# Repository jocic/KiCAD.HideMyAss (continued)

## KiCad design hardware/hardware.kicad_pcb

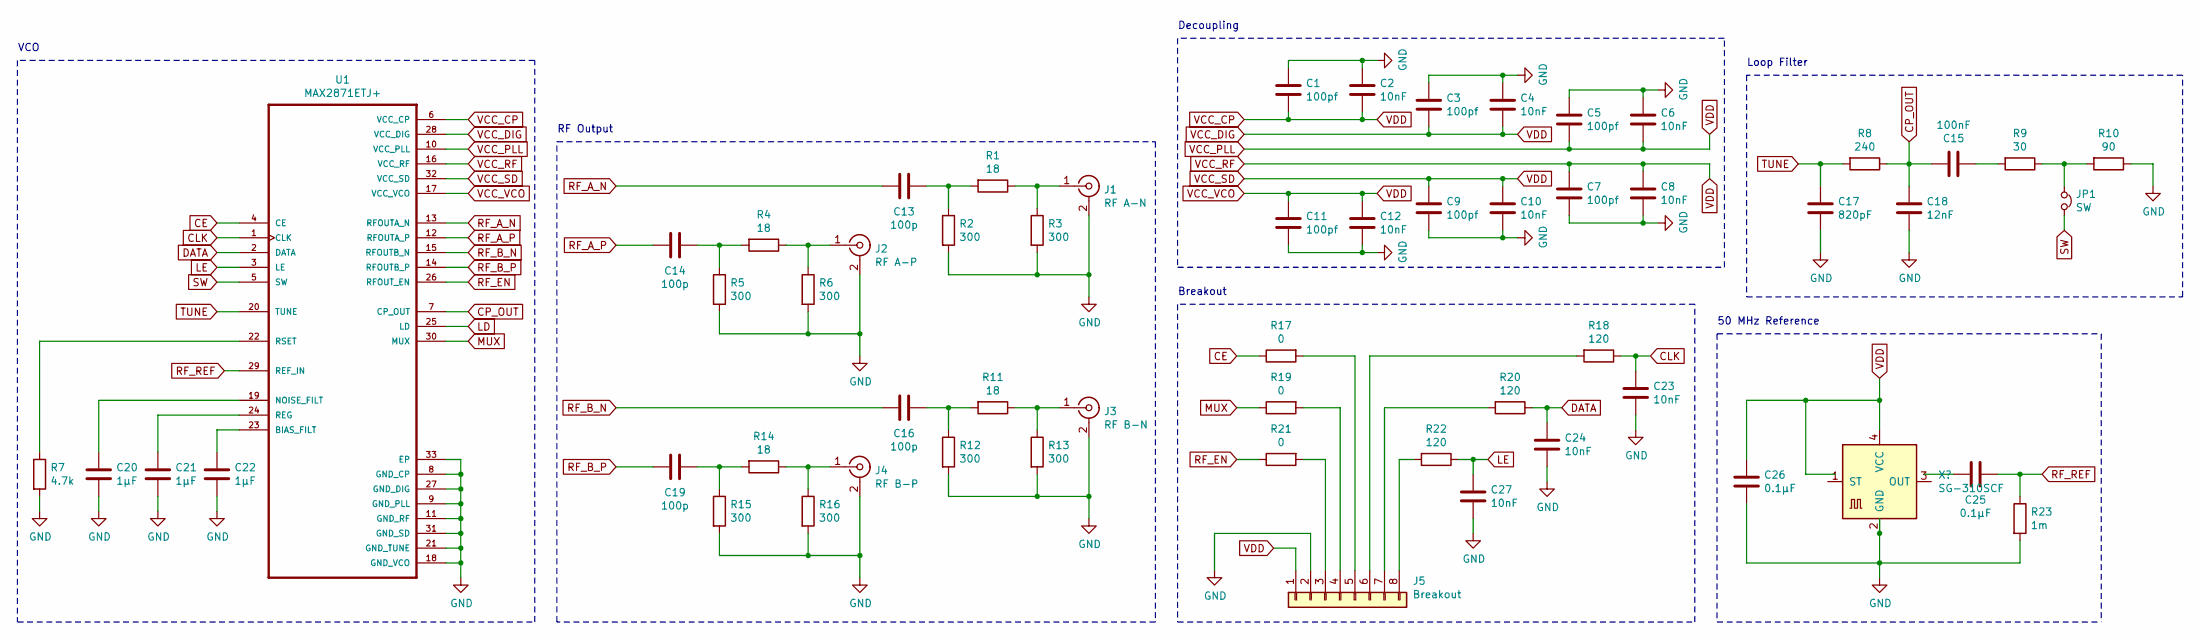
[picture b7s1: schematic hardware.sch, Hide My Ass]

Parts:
C1, C3, C5, C7, C9, C11: 100pf; C_0603_1608Metric_Pad1.05x0.95mm_HandSolder
C2, C4, C6, C8, C10, C12, C23, C24, C27: 10nF; C_0603_1608Metric_Pad1.05x0.95mm_HandSolder
C13, C14, C16, C19: 100p; C_0603_1608Metric_Pad1.05x0.95mm_HandSolder
C15: 100nF; C_0603_1608Metric_Pad1.05x0.95mm_HandSolder
C17: 820pF; C_0603_1608Metric_Pad1.05x0.95mm_HandSolder
C18: 12nF; C_0603_1608Metric_Pad1.05x0.95mm_HandSolder
C20, C21, C22: 1μF; C_0603_1608Metric_Pad1.05x0.95mm_HandSolder
C25, C26: 0.1μF; C_0603_1608Metric_Pad1.05x0.95mm_HandSolder
J1: RF A-N; SMA_Amphenol_901-144_Vertical
J2: RF A-P; SMA_Amphenol_901-144_Vertical
J3: RF B-N; SMA_Amphenol_901-144_Vertical
J4: RF B-P; SMA_Amphenol_901-144_Vertical
J5: Breakout; PinHeader_1x08_P2.54mm_Vertical
JP1: SW; PinHeader_1x02_P1.27mm_Vertical
R1, R4, R11, R14: 18; R_0603_1608Metric_Pad1.05x0.95mm_HandSolder
R2, R3, R5, R6, R12, R13, R15, R16: 300; R_0603_1608Metric_Pad1.05x0.95mm_HandSolder
R7: 4.7k; R_0603_1608Metric_Pad1.05x0.95mm_HandSolder
R8: 240; R_0603_1608Metric_Pad1.05x0.95mm_HandSolder
R9: 30; R_0603_1608Metric_Pad1.05x0.95mm_HandSolder
R10: 90; R_0603_1608Metric_Pad1.05x0.95mm_HandSolder
R17, R19, R21: 0; R_0603_1608Metric_Pad1.05x0.95mm_HandSolder
R18, R20, R22: 120; R_0603_1608Metric_Pad1.05x0.95mm_HandSolder
R23: 1m; R_0603_1608Metric_Pad1.05x0.95mm_HandSolder
U1: MAX2871ETJ+

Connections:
CE: R17.1, U1.4 (CE)
CLK: C23.1, R18.1, U1.1 (CLK)
CP_OUT: C15.2, C18.1, R8.1, U1.7 (CP_OUT)
DATA: C24.1, R20.1, U1.2 (DATA)
GND: C1.1, C2.1, C3.1, C4.1, C5.1, C6.1, C7.2, C8.2, C9.2, C10.2, C11.2, C12.2, C17.2, C18.2, C20.2, C21.2, C22.2, C23.2, C24.2, C26.2, C27.2, J1.2 (Ext), J2.2 (Ext), J3.2 (Ext), J4.2 (Ext), J5.2, R2.2, R3.2, R5.2, R6.2, R7.2, R10.1, R12.2, R13.2, R15.2, R16.2, R23.2, U1.8 (GND_CP), U1.9 (GND_PLL), U1.11 (GND_RF), U1.18 (GND_VCO), U1.21 (GND_TUNE), U1.27 (GND_DIG), U1.31 (GND_SD), U1.33 (EP); also elsewhere on the board
LD: U1.25 (LD)
LE: C27.1, R22.1, U1.3 (LE)
MUX: R19.1, U1.30 (MUX)
unnamed: C13.2, R1.2, R2.1
unnamed: C14.2, R4.2, R5.1
unnamed: C15.1, R9.2
unnamed: C16.2, R11.2, R12.1
unnamed: C19.2, R14.2, R15.1
unnamed: C20.1, U1.19 (NOISE_FILT)
unnamed: C21.1, U1.24 (REG)
unnamed: C22.1, U1.23 (BIAS_FILT)
unnamed 16: C25.1; also elsewhere on the board
unnamed: J1.1 (In), R1.1, R3.1
unnamed: J2.1 (In), R4.1, R6.1
unnamed: J3.1 (In), R11.1, R13.1
unnamed: J4.1 (In), R14.1, R16.1
unnamed: J5.3, R21.2
unnamed: J5.4, R19.2
unnamed: J5.5, R17.2
unnamed: J5.6, R18.2
unnamed: J5.7, R20.2
unnamed: J5.8, R22.2
unnamed: JP1.1, R9.1, R10.2
unnamed: R7.1, U1.22 (RSET)
RF_A_N: C13.1, U1.13 (RFOUTA_N)
RF_A_P: C14.1, U1.12 (RFOUTA_P)
RF_B_N: C16.1, U1.15 (RFOUTB_N)
RF_B_P: C19.1, U1.14 (RFOUTB_P)
RF_EN: R21.1, U1.26 (RFOUT_EN)
RF_REF: C25.2, R23.1, U1.29 (REF_IN)
SW: JP1.2, U1.5 (SW)
TUNE: C17.1, R8.2, U1.20 (TUNE)
VCC_CP: C1.2, C2.2, C3.2, C4.2, C5.2, C6.2, C7.1, C8.1, C9.1, C10.1, C11.1, C12.1, C26.1, J5.1, U1.6 (VCC_CP), U1.10 (VCC_PLL), U1.16 (VCC_RF), U1.17 (VCC_VCO), U1.28 (VCC_DIG), U1.32 (VCC_SD); also elsewhere on the board

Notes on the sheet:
50 MHz Reference
Decoupling
RF Output
Breakout
Loop Filter
VCO

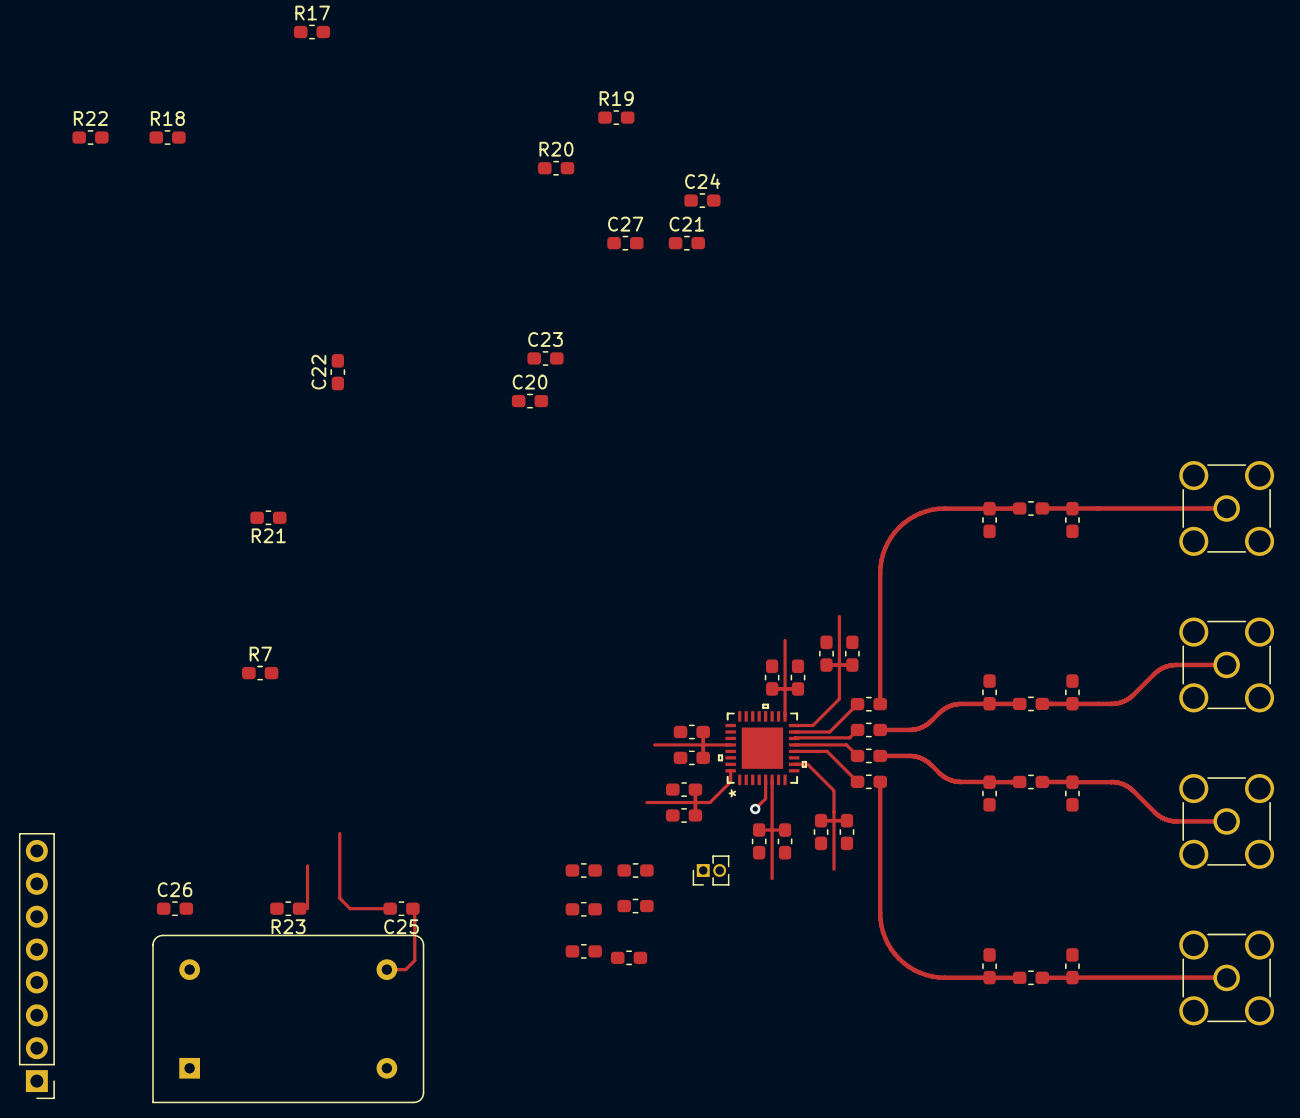
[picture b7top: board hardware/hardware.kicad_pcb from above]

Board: 4 copper layers, 58 parts (0 on the bottom side), 37 nets.

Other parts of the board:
X1: CXO_DIP14; Oscillator_DIP-14

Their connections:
GND: X1.7; also elsewhere on the board
unnamed 16: X1.8; also elsewhere on the board
VCC_CP: X1.1, X1.14; also elsewhere on the board

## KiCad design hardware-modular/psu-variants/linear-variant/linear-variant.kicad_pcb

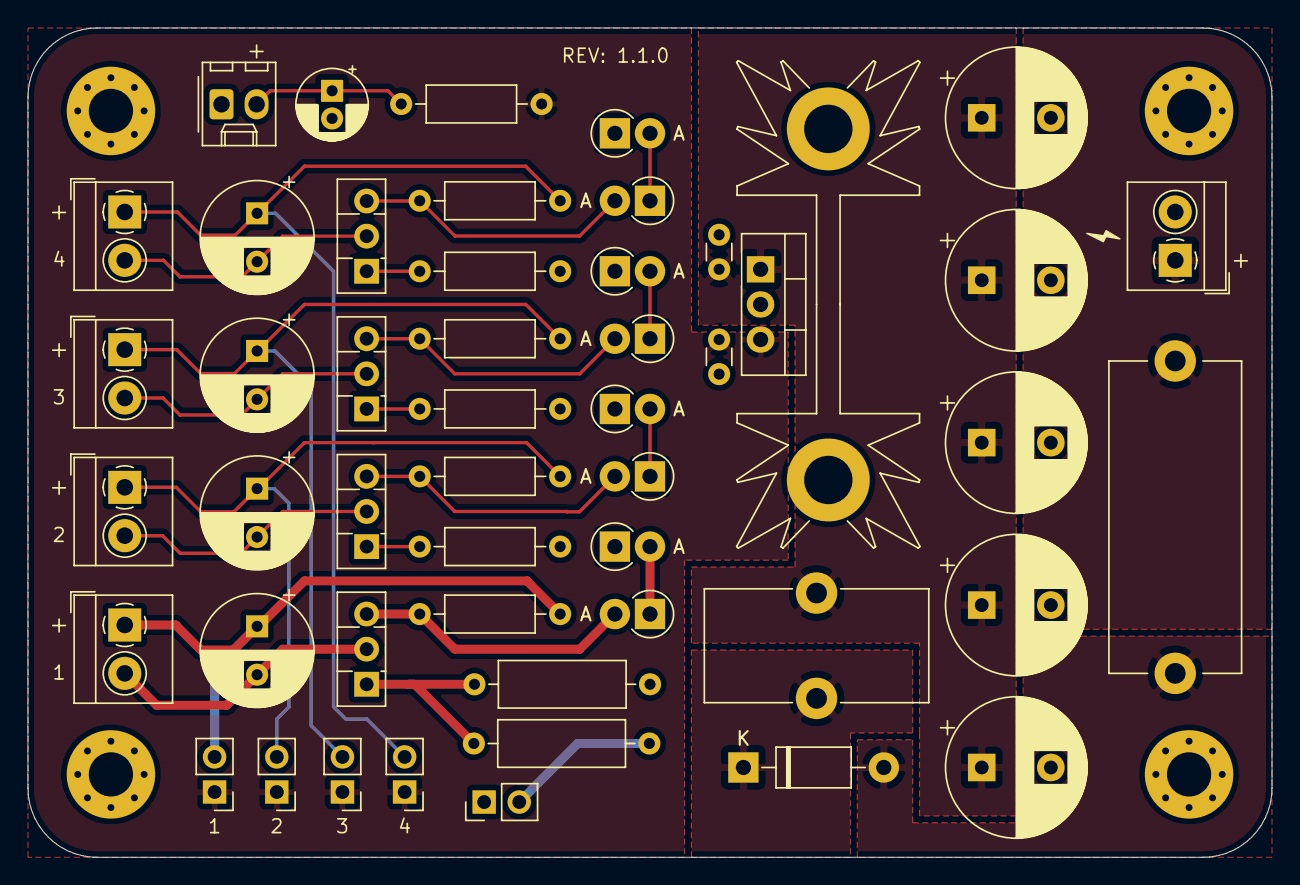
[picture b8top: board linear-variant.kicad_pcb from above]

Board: 2 copper layers, 90.0 x 60.0 mm, 54 parts (0 on the bottom side), 28 nets.

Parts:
C1, C2, C3: 1mF; CP_Radial_D10.0mm_P5.00mm
C4, C5: 470µF; CP_Radial_D10.0mm_P5.00mm
C6: 0.33µF; C_Disc_D3.0mm_W1.6mm_P2.50mm
C7: 0.1µF; C_Disc_D3.0mm_W1.6mm_P2.50mm
C8: 100µF; CP_Radial_D5.0mm_P2.00mm
C9, C10, C11, C12: 1mF; CP_Radial_D8.0mm_P3.50mm
D1: 1N4007; D_DO-41_SOD81_P10.16mm_Horizontal
D2: RED; Molex_KK-254_AE-6410-02A_1x02_P2.54mm_Vertical
D3, D4, D5, D6, D7, D8, D9, D10: 1N4007; D_DO-41_SOD81_P2.54mm_Vertical_AnodeUp
F1: 2A; Fuseholder_Cylinder-5x20mm_Stelvio-Kontek_PTF78_Horizontal_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
H1, H2, H3, H4: Mounting Pad; MountingHole_3.2mm_M3_Pad_Via
HS1: Heatsink; Heatsink_Fischer_SK104-STCB_35x13mm__2xDrill3.5mm_ScrewM3
J1: DC_IN; TerminalBlock_4Ucon_1x02_P3.50mm_Horizontal
J2: DC_OUT_1; TerminalBlock_4Ucon_1x02_P3.50mm_Horizontal
J3: DC_OUT_2; TerminalBlock_4Ucon_1x02_P3.50mm_Horizontal
J4: DC_OUT_3; TerminalBlock_4Ucon_1x02_P3.50mm_Horizontal
J5: DC_OUT_4; TerminalBlock_4Ucon_1x02_P3.50mm_Horizontal
JP1, JP2, JP3, JP4, JP5: GATE; PinHeader_1x02_P2.54mm_Vertical
L1: 100µF; L_Toroid_Vertical_L16.0mm_W8.0mm_P7.62mm
Q1, Q2, Q3, Q4: BD137; TO-126-3_Vertical
R1, R2, R3, R4, R5: 100; R_Axial_DIN0207_L6.3mm_D2.5mm_P10.16mm_Horizontal
R6, R7: 2.2; R_Axial_DIN0309_L9.0mm_D3.2mm_P12.70mm_Horizontal
R8, R9, R10: 2.2; R_Axial_DIN0207_L6.3mm_D2.5mm_P10.16mm_Horizontal
U1: L7805; TO-220-3_Vertical

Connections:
+12V: F1.2, J1.1
GND: C1.2, C2.2, C3.2, C4.2, C5.2, C6.2, C7.2, C8.2, D2.1, D4.1, D6.1, D8.1, D10.1, H1.1, H2.1, H3.1, H4.1, HS1.1, J1.2, JP5.1, R6.1, R8.1, R9.1, R10.1, U1.2
unnamed: C1.1, C2.1, C3.1, C4.1, C5.1, C6.1, L1.2, U1.1
unnamed: C8.1, D2.2, R1.1
unnamed: C9.1, J2.1, JP1.2, R2.1
unnamed: C9.2, J2.2, Q1.2
unnamed: C10.1, J3.1, JP2.2, R3.1
unnamed: C10.2, J3.2, Q2.2
unnamed: C11.1, J4.1, JP3.2, R4.1
unnamed: C11.2, J4.2, Q3.2
unnamed: C12.1, J5.1, JP4.2, R5.1
unnamed: C12.2, J5.2, Q4.2
unnamed: D1.1, L1.1
unnamed: D1.2, F1.1
unnamed: D3.1, D4.2
unnamed: D3.2, Q1.3, R2.2
unnamed: D5.1, D6.2
unnamed: D5.2, Q2.3, R3.2
unnamed: D7.1, D8.2
unnamed: D7.2, Q3.3, R4.2
unnamed: D9.2, Q4.3, R5.2
unnamed: D9.1, D10.2
unnamed: JP5.2, R7.2
unnamed: Q1.1, R6.2, R7.1
unnamed: Q2.1, R8.2
unnamed: Q3.1, R9.2
unnamed: Q4.1, R10.2
OUT: C7.1, JP1.1, JP2.1, JP3.1, JP4.1, R1.2, U1.3

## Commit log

2020-07-15 Project initialization.
2020-08-23 USB Connection & ESD Protection.
2020-08-23 3.3V Voltage Regulator.
2020-08-24 Battery protection circuit.
2020-08-24 Battery management circuit.
2020-08-24 Basic MCU wiring for a test batch.
2020-08-24 Assigned footprints to the project.
2020-08-24 MAX2871 datasheet & footprint.
2020-08-24 Compacted schematics.
2020-08-24 50 MHz reference.
2020-08-24 MAX2871 decoupling.
2020-09-01 Added CVCO55 footprint, symbol & 3D model.
2020-09-01 Added NLB-310 footprint, symbol & 3D model.
2020-09-02 500-1000 MHz & 1000-2000 MHz Crystek VCOs.
2020-09-03 1600-3200 MHz & 3180-3710 MHz Crystek VCOs.
2020-09-04 Additional VCOs for 100-500 MHz range.
2020-09-05 Assigned footprints & part IDs.
2020-09-05 Added CVCO datasheets.
2020-09-06 Pover supply for CVCO variant.
2020-09-06 Battery management for CVCO variant.
2020-09-06 24V boost circuit added - CVCO.
2020-09-19 Updated schematic for Maxim version.
2020-09-19 Added TQFN-32 model.
2020-09-19 Fixed minor issue with RF Output.
2020-09-27 VCO switcher.
2020-09-27 IC buffer added.
2020-09-27 Noise Source & Summer added.
2020-09-30 Simplified CVCO design.
2020-09-30 LCSC part numbers assigned.
2020-09-30 RF layout - start.
2020-10-02 RF section layout finished - CVCO.
2020-10-02 Added horizontal Molex footprint & 3D model.
2020-10-02 Rough layout of the non-RF section.
2020-10-03 Added icons & icon footprints - CVCO.
2020-10-03 Replaced FA icons.
2020-10-03 Assigned LCSC parts to battery mng. section.
2020-10-03 Replaced LM358 with LM324.
2020-10-03 Non-RF section layout finished - CVCO.
2020-10-03 RF section routing - CVCO.
2020-10-04 Power Supply & Battery Management routing - CVCO.
2020-10-04 Sweep Generator routing - CVCO.
2020-10-04 Noise Source routing - CVCO.
2020-10-05 PIC routing - CVCO.
2020-10-05 Updated RF section - CVCO.
2020-10-06 Buffer routing - CVCO.
2020-10-10 RF Section Buffer routing - CVCO.
2020-10-10 RF shield - CVCO.
2020-10-10 Redone RF shield - CVCO.
2020-10-11 Finalized CVCO variant.
2020-10-11 BOM & Gerber files - CVCO.
2020-10-13 200-400 MHz MOSFET VCO - Schema.
2020-10-24 Boost circuit update.
2020-10-24 Boost circuit update - PCB.
2020-10-24 Battery managment, boost & sweep - discrete.
2020-10-30 Power Supply & Battery Management update.
2020-10-31 Temperature control.
2020-11-01 Battery management software - untested.
2020-11-01 Battery management update.
2020-11-02 Battery management code finalization.
2020-11-03 Charging switch.
2020-11-04 Minor tweaks to battery management.
2020-11-05 Noise source for discrete version.
2021-01-23 PSU module.
2021-01-24 Li-Po charger module - schema.
2021-01-26 Li-Po charger module - PCB.
2021-01-26 Gerber files - PSU.
2021-01-26 Gerber files - Charger.
2021-01-26 Generated BOM for PSU & Charger mod.
2021-02-01 RF Amplifier module - ADL.
2021-02-01 RF Amplifier module - NLB.
2021-02-01 Tweaked amplifier modules.
2021-02-01 Trans. line width issue resolved - amp. modules.
2021-02-07 CVCO 500-1000 MHz module - Schema.
2021-02-09 CVCO 500-1000 MHz module - PCB.
2021-02-09 CVCO 500-1000 MHz module - Gerber Files.
2021-02-11 PSU module revision.
2021-02-12 PWM management - charger module.
2021-02-12 Temp & Bat probe - charger module.
2021-02-13 Firmware for the charger module.
2021-02-13 Renamed firmware directory.
2021-02-22 Moved PSU module.
2021-02-22 Fixed 3D model paths - PSU (linear).
2021-02-23 CVCO general module.
2021-02-23 Removed VCO variant.
